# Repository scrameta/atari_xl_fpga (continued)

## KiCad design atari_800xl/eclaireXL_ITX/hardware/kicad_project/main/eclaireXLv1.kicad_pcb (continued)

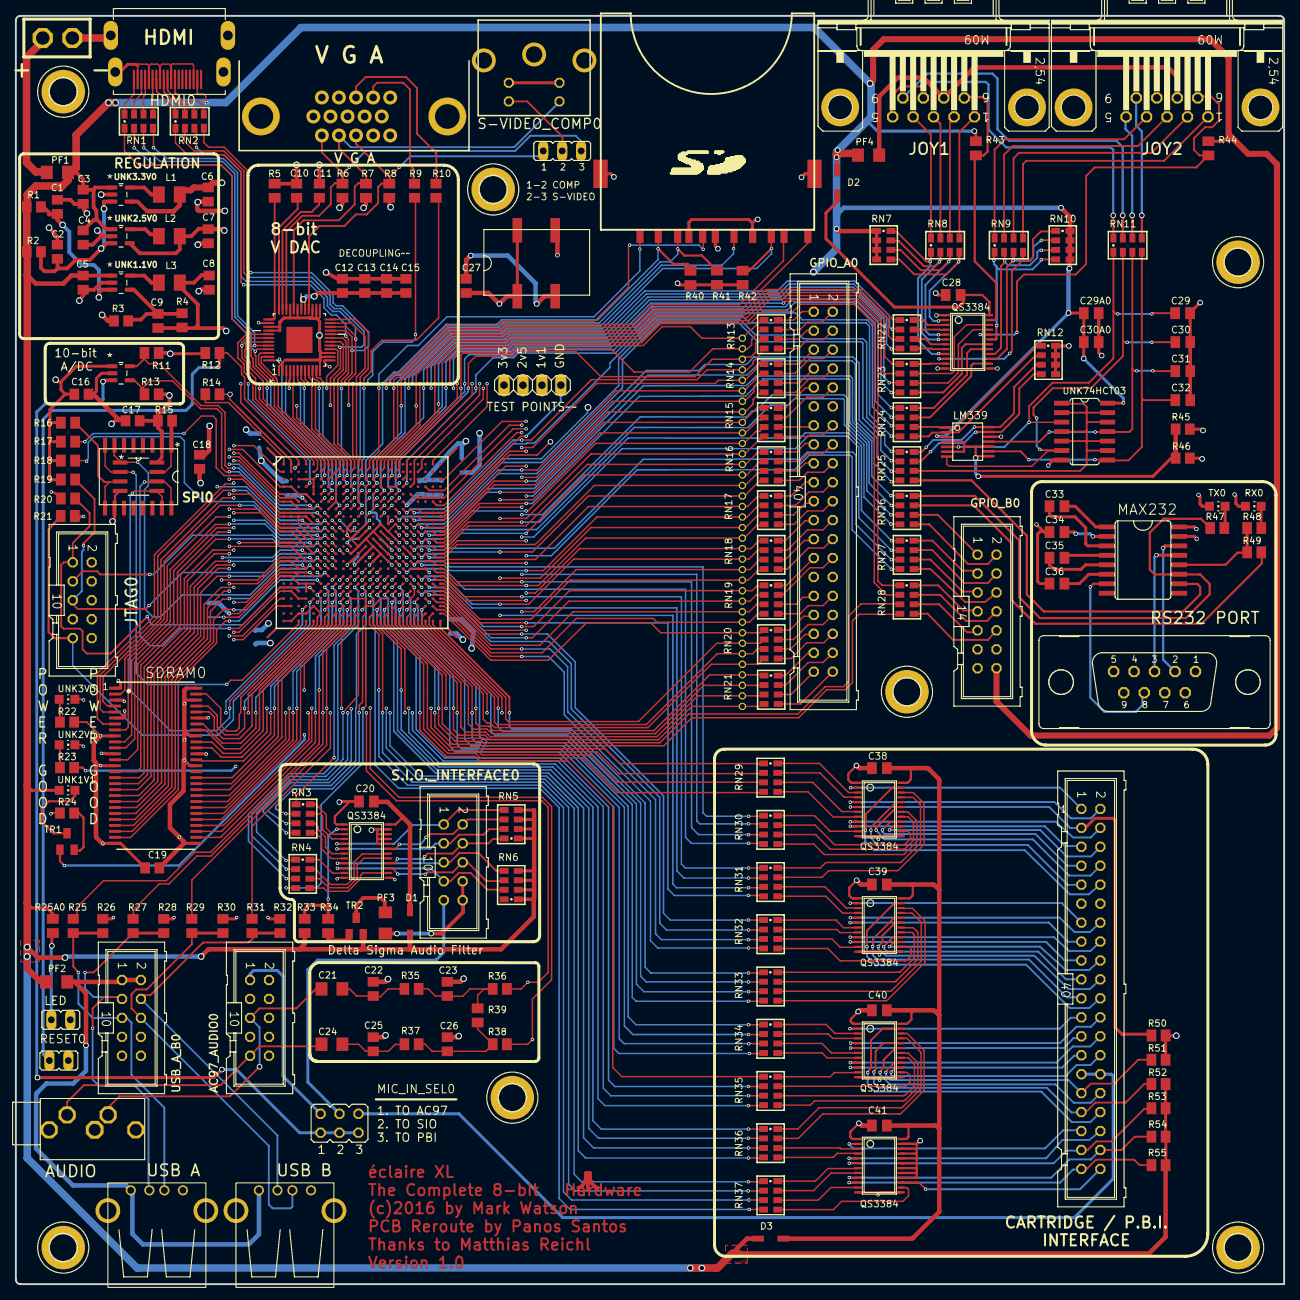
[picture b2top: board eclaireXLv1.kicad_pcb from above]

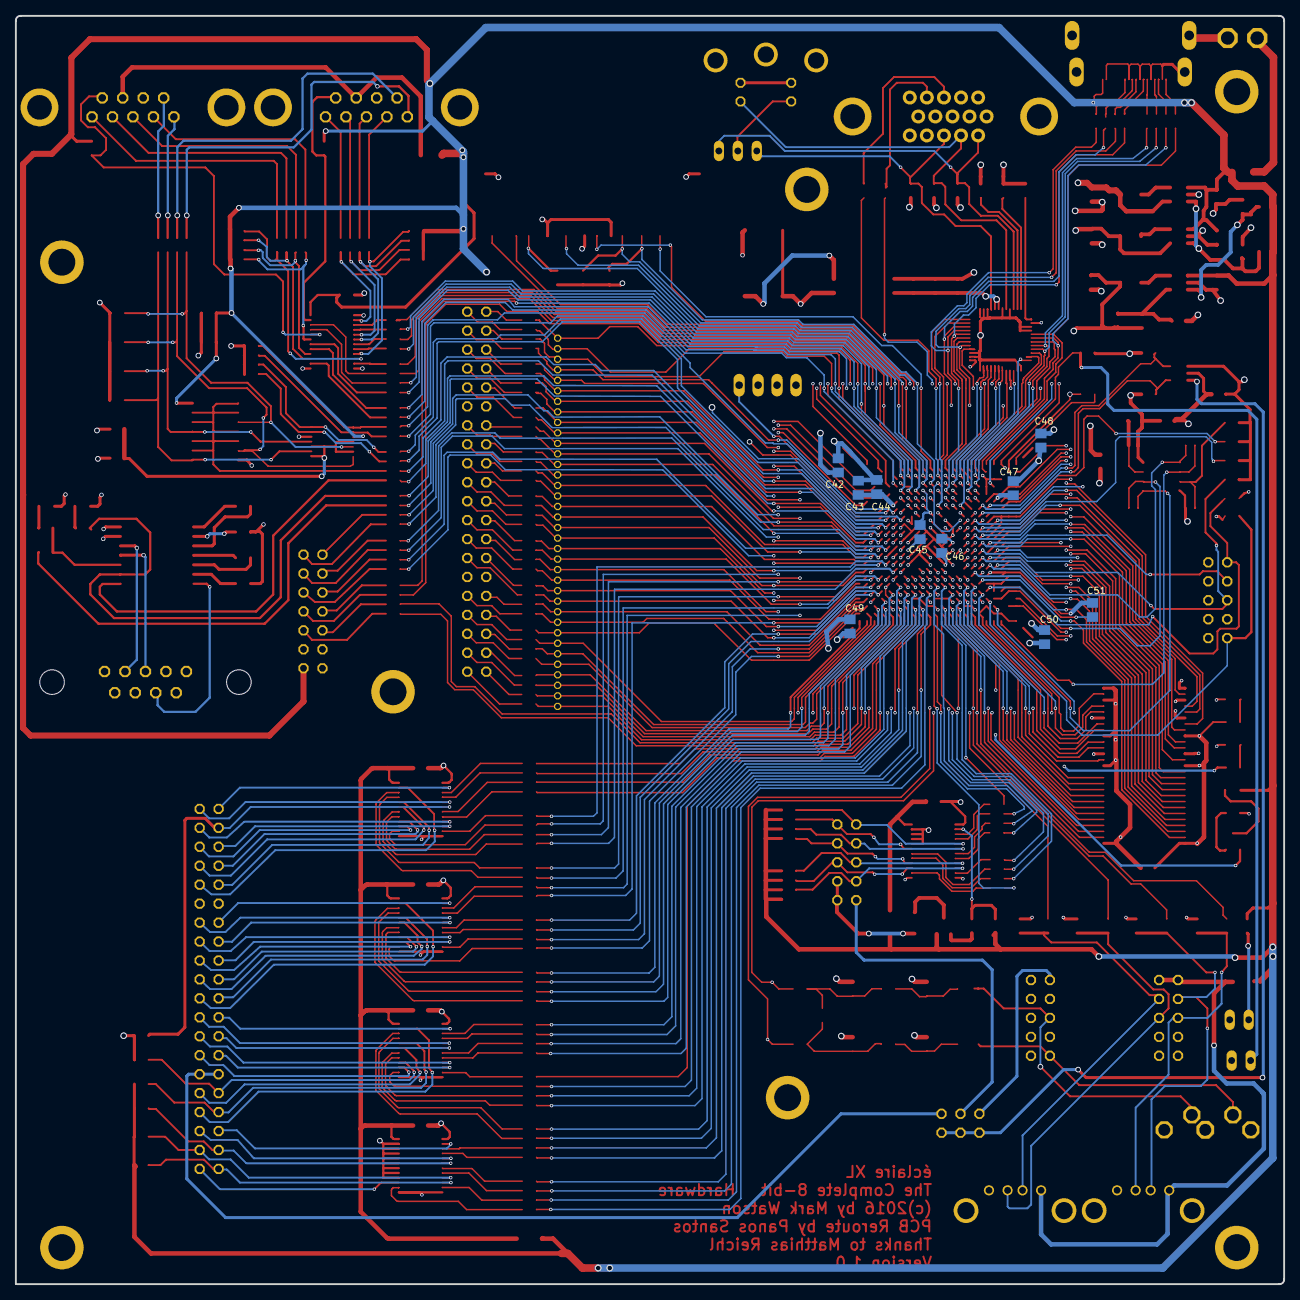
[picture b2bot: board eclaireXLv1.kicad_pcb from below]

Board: 4 copper layers, 170.0 x 170.0 mm, 211 parts (10 on the bottom side), 453 nets.

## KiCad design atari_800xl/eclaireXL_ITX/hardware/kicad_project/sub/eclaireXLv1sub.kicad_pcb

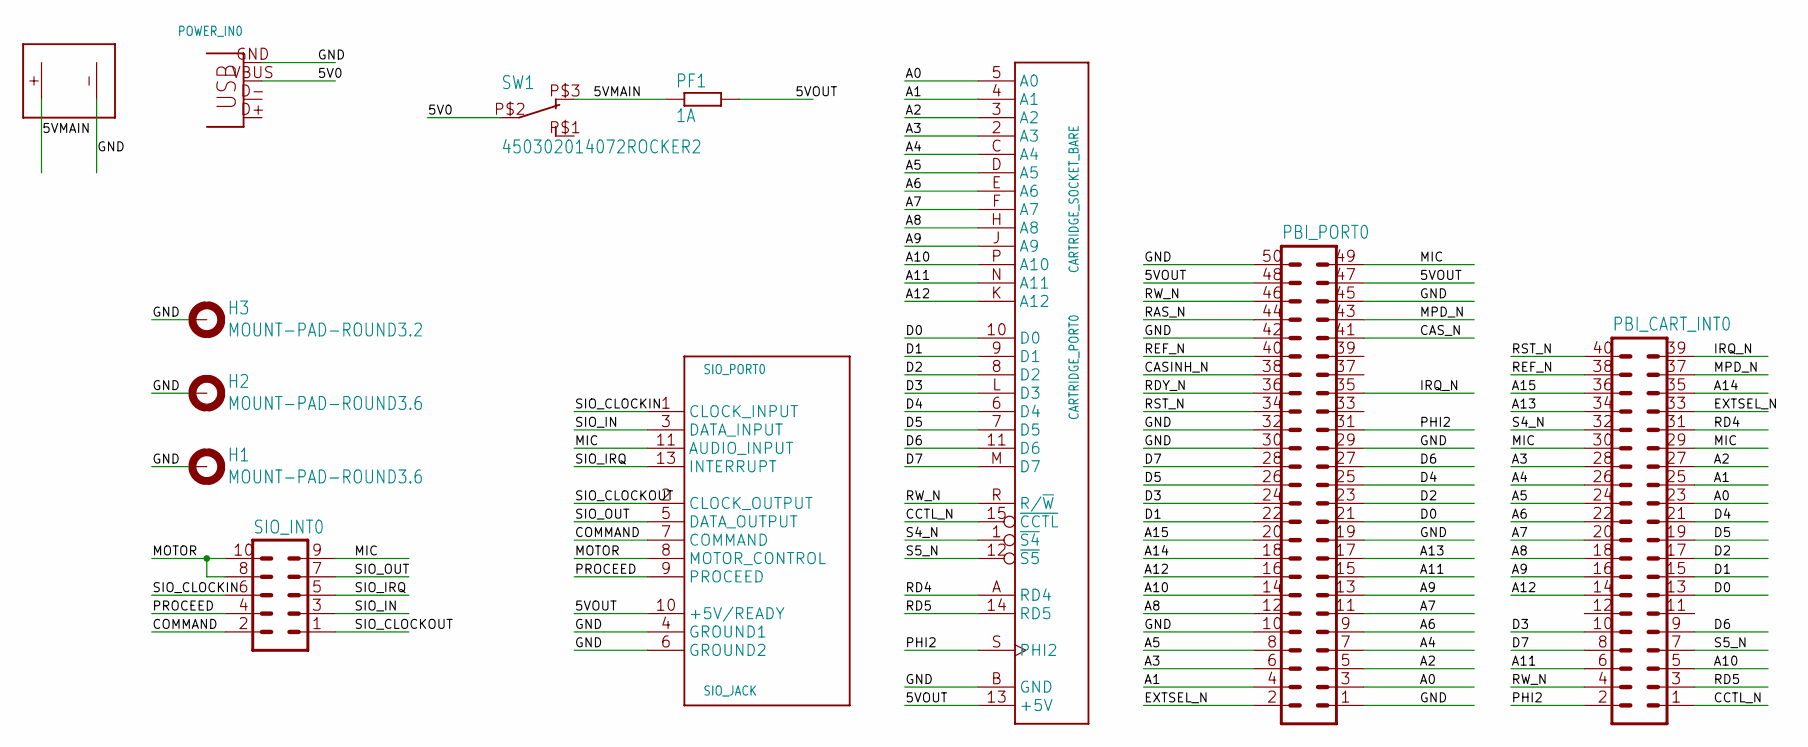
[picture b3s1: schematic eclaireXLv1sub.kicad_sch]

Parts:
CARTRIDGE_PORT0: CARTRIDGE_SOCKET_BARE; CARTRIDGE_SOCKET
H1, H2: MOUNT-PAD-ROUND3.6; 3,6-PAD
H3: MOUNT-PAD-ROUND3.2; 3,2-PAD
PBI_CART_INT0: ML40
PBI_PORT0: ML50
PF1: 1A; R1206
POWER_IN0: USB-B-H
SIO_INT0: ML10
SIO_PORT0: SIO_JACK
SW1: 450302014072ROCKER2; ROCKER_VERT_SPDT2
U$6: MOLEX_PS

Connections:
5V0: POWER_IN0.VBUS, SW1.P$2 (1)
5VMAIN: PF1.1, SW1.P$3 (3), U$6.+
5VOUT: CARTRIDGE_PORT0.13 (+5V), PBI_PORT0.47, PBI_PORT0.48, PF1.2, SIO_PORT0.10 (+5V/READY)
A0: CARTRIDGE_PORT0.5 (A0), PBI_CART_INT0.23, PBI_PORT0.3
A1: CARTRIDGE_PORT0.4 (A1), PBI_CART_INT0.25, PBI_PORT0.4
A2: CARTRIDGE_PORT0.3 (A2), PBI_CART_INT0.27, PBI_PORT0.5
A3: CARTRIDGE_PORT0.2 (A3), PBI_CART_INT0.28, PBI_PORT0.6
A4: CARTRIDGE_PORT0.C (A4), PBI_CART_INT0.26, PBI_PORT0.7
A5: CARTRIDGE_PORT0.D (A5), PBI_CART_INT0.24, PBI_PORT0.8
A6: CARTRIDGE_PORT0.E (A6), PBI_CART_INT0.22, PBI_PORT0.9
A7: CARTRIDGE_PORT0.F (A7), PBI_CART_INT0.20, PBI_PORT0.11
A8: CARTRIDGE_PORT0.H (A8), PBI_CART_INT0.18, PBI_PORT0.12
A9: CARTRIDGE_PORT0.J (A9), PBI_CART_INT0.16, PBI_PORT0.13
A10: CARTRIDGE_PORT0.P (A10), PBI_CART_INT0.5, PBI_PORT0.14
A11: CARTRIDGE_PORT0.N (A11), PBI_CART_INT0.6, PBI_PORT0.15
A12: CARTRIDGE_PORT0.K (A12), PBI_CART_INT0.14, PBI_PORT0.16
A13: PBI_CART_INT0.34, PBI_PORT0.17
A14: PBI_CART_INT0.35, PBI_PORT0.18
A15: PBI_CART_INT0.36, PBI_PORT0.20
CASINH_N: PBI_PORT0.38
CAS_N: PBI_PORT0.41
CCTL_N: CARTRIDGE_PORT0.15 (~CCTL), PBI_CART_INT0.1
COMMAND: SIO_INT0.2, SIO_PORT0.7 (COMMAND)
D0: CARTRIDGE_PORT0.10 (D0), PBI_CART_INT0.13, PBI_PORT0.21
D1: CARTRIDGE_PORT0.9 (D1), PBI_CART_INT0.15, PBI_PORT0.22
D2: CARTRIDGE_PORT0.8 (D2), PBI_CART_INT0.17, PBI_PORT0.23
D3: CARTRIDGE_PORT0.L (D3), PBI_CART_INT0.10, PBI_PORT0.24
D4: CARTRIDGE_PORT0.6 (D4), PBI_CART_INT0.21, PBI_PORT0.25
D5: CARTRIDGE_PORT0.7 (D5), PBI_CART_INT0.19, PBI_PORT0.26
D6: CARTRIDGE_PORT0.11 (D6), PBI_CART_INT0.9, PBI_PORT0.27
D7: CARTRIDGE_PORT0.M (D7), PBI_CART_INT0.8, PBI_PORT0.28
EXTSEL_N: PBI_CART_INT0.33, PBI_PORT0.2
GND: CARTRIDGE_PORT0.B (GND), H1.B3,6, H2.B3,6, H3.B3,2, PBI_PORT0.1, PBI_PORT0.10, PBI_PORT0.19, PBI_PORT0.29, PBI_PORT0.30, PBI_PORT0.32, PBI_PORT0.42, PBI_PORT0.45, PBI_PORT0.50, POWER_IN0.GND, SIO_PORT0.4 (GROUND1), SIO_PORT0.6 (GROUND2), U$6.- (--)
IRQ_N: PBI_CART_INT0.39, PBI_PORT0.35
MIC: PBI_CART_INT0.29, PBI_CART_INT0.30, PBI_PORT0.49, SIO_INT0.9, SIO_PORT0.11 (AUDIO_INPUT)
MOTOR: SIO_INT0.8, SIO_INT0.10, SIO_PORT0.8 (MOTOR_CONTROL)
MPD_N: PBI_CART_INT0.37, PBI_PORT0.43
PHI2: CARTRIDGE_PORT0.S (PHI2), PBI_CART_INT0.2, PBI_PORT0.31
PROCEED: SIO_INT0.4, SIO_PORT0.9 (PROCEED)
RAS_N: PBI_PORT0.44
RD4: CARTRIDGE_PORT0.A (RD4), PBI_CART_INT0.31
RD5: CARTRIDGE_PORT0.14 (RD5), PBI_CART_INT0.3
RDY_N: PBI_PORT0.36
REF_N: PBI_CART_INT0.38, PBI_PORT0.40
RST_N: PBI_CART_INT0.40, PBI_PORT0.34
RW_N: CARTRIDGE_PORT0.R (R/~W), PBI_CART_INT0.4, PBI_PORT0.46
S4_N: CARTRIDGE_PORT0.1 (~S4), PBI_CART_INT0.32
S5_N: CARTRIDGE_PORT0.12 (~S5), PBI_CART_INT0.7
SIO_CLOCKIN: SIO_INT0.6, SIO_PORT0.1 (CLOCK_INPUT)
SIO_CLOCKOUT: SIO_INT0.1, SIO_PORT0.2 (CLOCK_OUTPUT)
SIO_IN: SIO_INT0.3, SIO_PORT0.3 (DATA_INPUT)
SIO_IRQ: SIO_INT0.5, SIO_PORT0.13 (INTERRUPT)
SIO_OUT: SIO_INT0.7, SIO_PORT0.5 (DATA_OUTPUT)

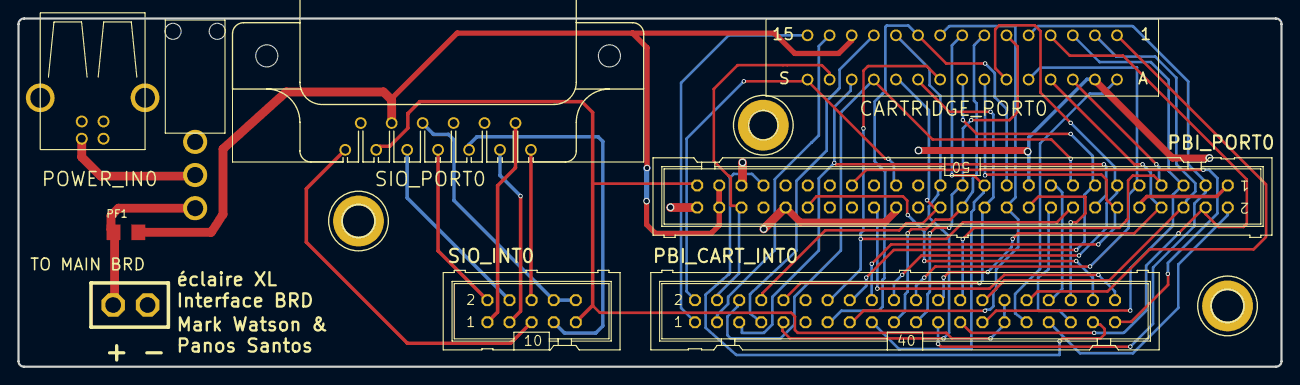
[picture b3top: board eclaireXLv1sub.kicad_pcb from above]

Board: 4 copper layers, 145.1 x 40.0 mm, 12 parts (0 on the bottom side), 49 nets.

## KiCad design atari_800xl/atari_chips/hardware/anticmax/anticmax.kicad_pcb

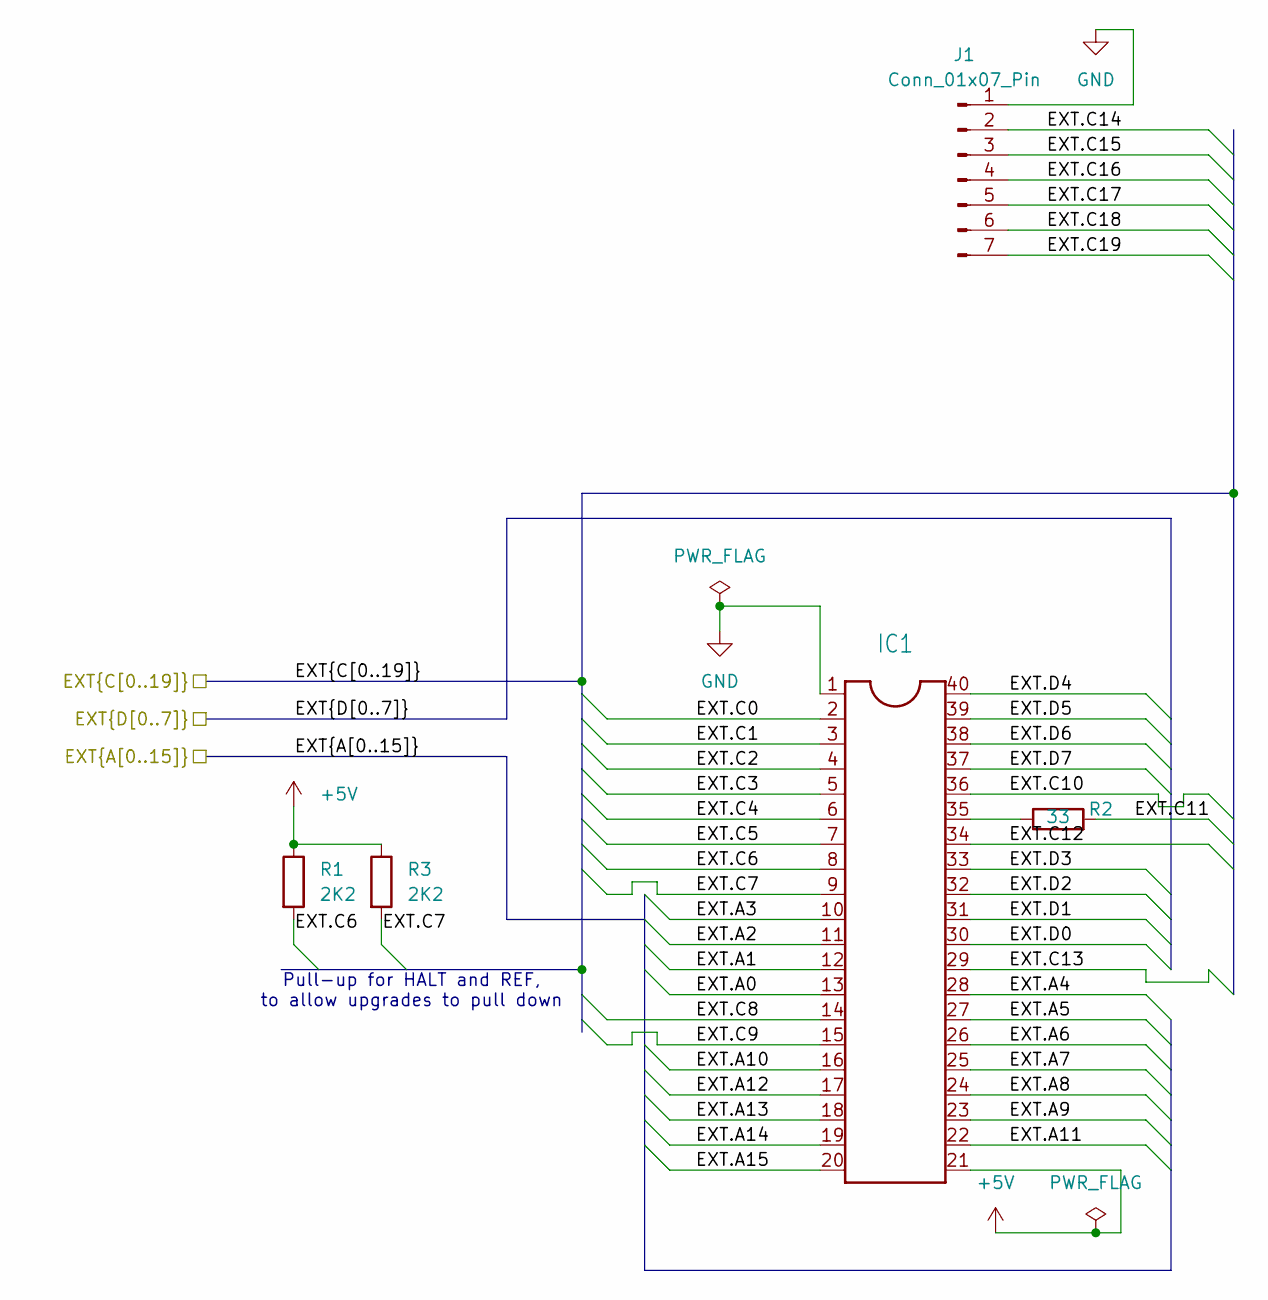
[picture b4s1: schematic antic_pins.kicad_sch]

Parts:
IC1: DIL40
J1: Conn_01x07_Pin; PinHeader_1x07_P2.54mm_Vertical
R1, R3: 2K2; R_0603_1608Metric
R2: 33; R_0603_1608Metric

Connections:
+5V: IC1.21, R1.1, R3.1; also elsewhere on the board
/Bus drivers/EXT.A0: IC1.13; also elsewhere on the board
/Bus drivers/EXT.A1: IC1.12; also elsewhere on the board
/Bus drivers/EXT.A2: IC1.11; also elsewhere on the board
/Bus drivers/EXT.A3: IC1.10; also elsewhere on the board
/Bus drivers/EXT.A4: IC1.28; also elsewhere on the board
/Bus drivers/EXT.A5: IC1.27; also elsewhere on the board
/Bus drivers/EXT.A6: IC1.26; also elsewhere on the board
/Bus drivers/EXT.A7: IC1.25; also elsewhere on the board
/Bus drivers/EXT.A8: IC1.24; also elsewhere on the board
/Bus drivers/EXT.A9: IC1.23; also elsewhere on the board
/Bus drivers/EXT.A10: IC1.16; also elsewhere on the board
/Bus drivers/EXT.A11: IC1.22; also elsewhere on the board
/Bus drivers/EXT.A12: IC1.17; also elsewhere on the board
/Bus drivers/EXT.A13: IC1.18; also elsewhere on the board
/Bus drivers/EXT.A14: IC1.19; also elsewhere on the board
/Bus drivers/EXT.A15: IC1.20; also elsewhere on the board
/Bus drivers/EXT.D0: IC1.30; also elsewhere on the board
/Bus drivers/EXT.D1: IC1.31; also elsewhere on the board
/Bus drivers/EXT.D2: IC1.32; also elsewhere on the board
/Bus drivers/EXT.D3: IC1.33; also elsewhere on the board
/Bus drivers/EXT.D4: IC1.40; also elsewhere on the board
/Bus drivers/EXT.D5: IC1.39; also elsewhere on the board
/Bus drivers/EXT.D6: IC1.38; also elsewhere on the board
/Bus drivers/EXT.D7: IC1.37; also elsewhere on the board
/antic_pins/EXT.C0: IC1.2; also elsewhere on the board
/antic_pins/EXT.C1: IC1.3; also elsewhere on the board
/antic_pins/EXT.C2: IC1.4; also elsewhere on the board
/antic_pins/EXT.C3: IC1.5; also elsewhere on the board
/antic_pins/EXT.C4: IC1.6; also elsewhere on the board
/antic_pins/EXT.C5: IC1.7; also elsewhere on the board
/antic_pins/EXT.C6: IC1.8, R1.2; also elsewhere on the board
/antic_pins/EXT.C7: IC1.9, R3.2; also elsewhere on the board
/antic_pins/EXT.C8: IC1.14; also elsewhere on the board
/antic_pins/EXT.C9: IC1.15; also elsewhere on the board
/antic_pins/EXT.C10: IC1.36; also elsewhere on the board
/antic_pins/EXT.C11: R2.2; also elsewhere on the board
/antic_pins/EXT.C12: IC1.34; also elsewhere on the board
/antic_pins/EXT.C13: IC1.29; also elsewhere on the board
/antic_pins/EXT.C14: J1.2; also elsewhere on the board
/antic_pins/EXT.C15: J1.3; also elsewhere on the board
/antic_pins/EXT.C16: J1.4; also elsewhere on the board
/antic_pins/EXT.C17: J1.5; also elsewhere on the board
/antic_pins/EXT.C18: J1.6; also elsewhere on the board
/antic_pins/EXT.C19: J1.7; also elsewhere on the board
GND: IC1.1, J1.1; also elsewhere on the board
unnamed: IC1.35, R2.1

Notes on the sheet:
Pull-up for HALT and REF, to allow upgrades to pull down

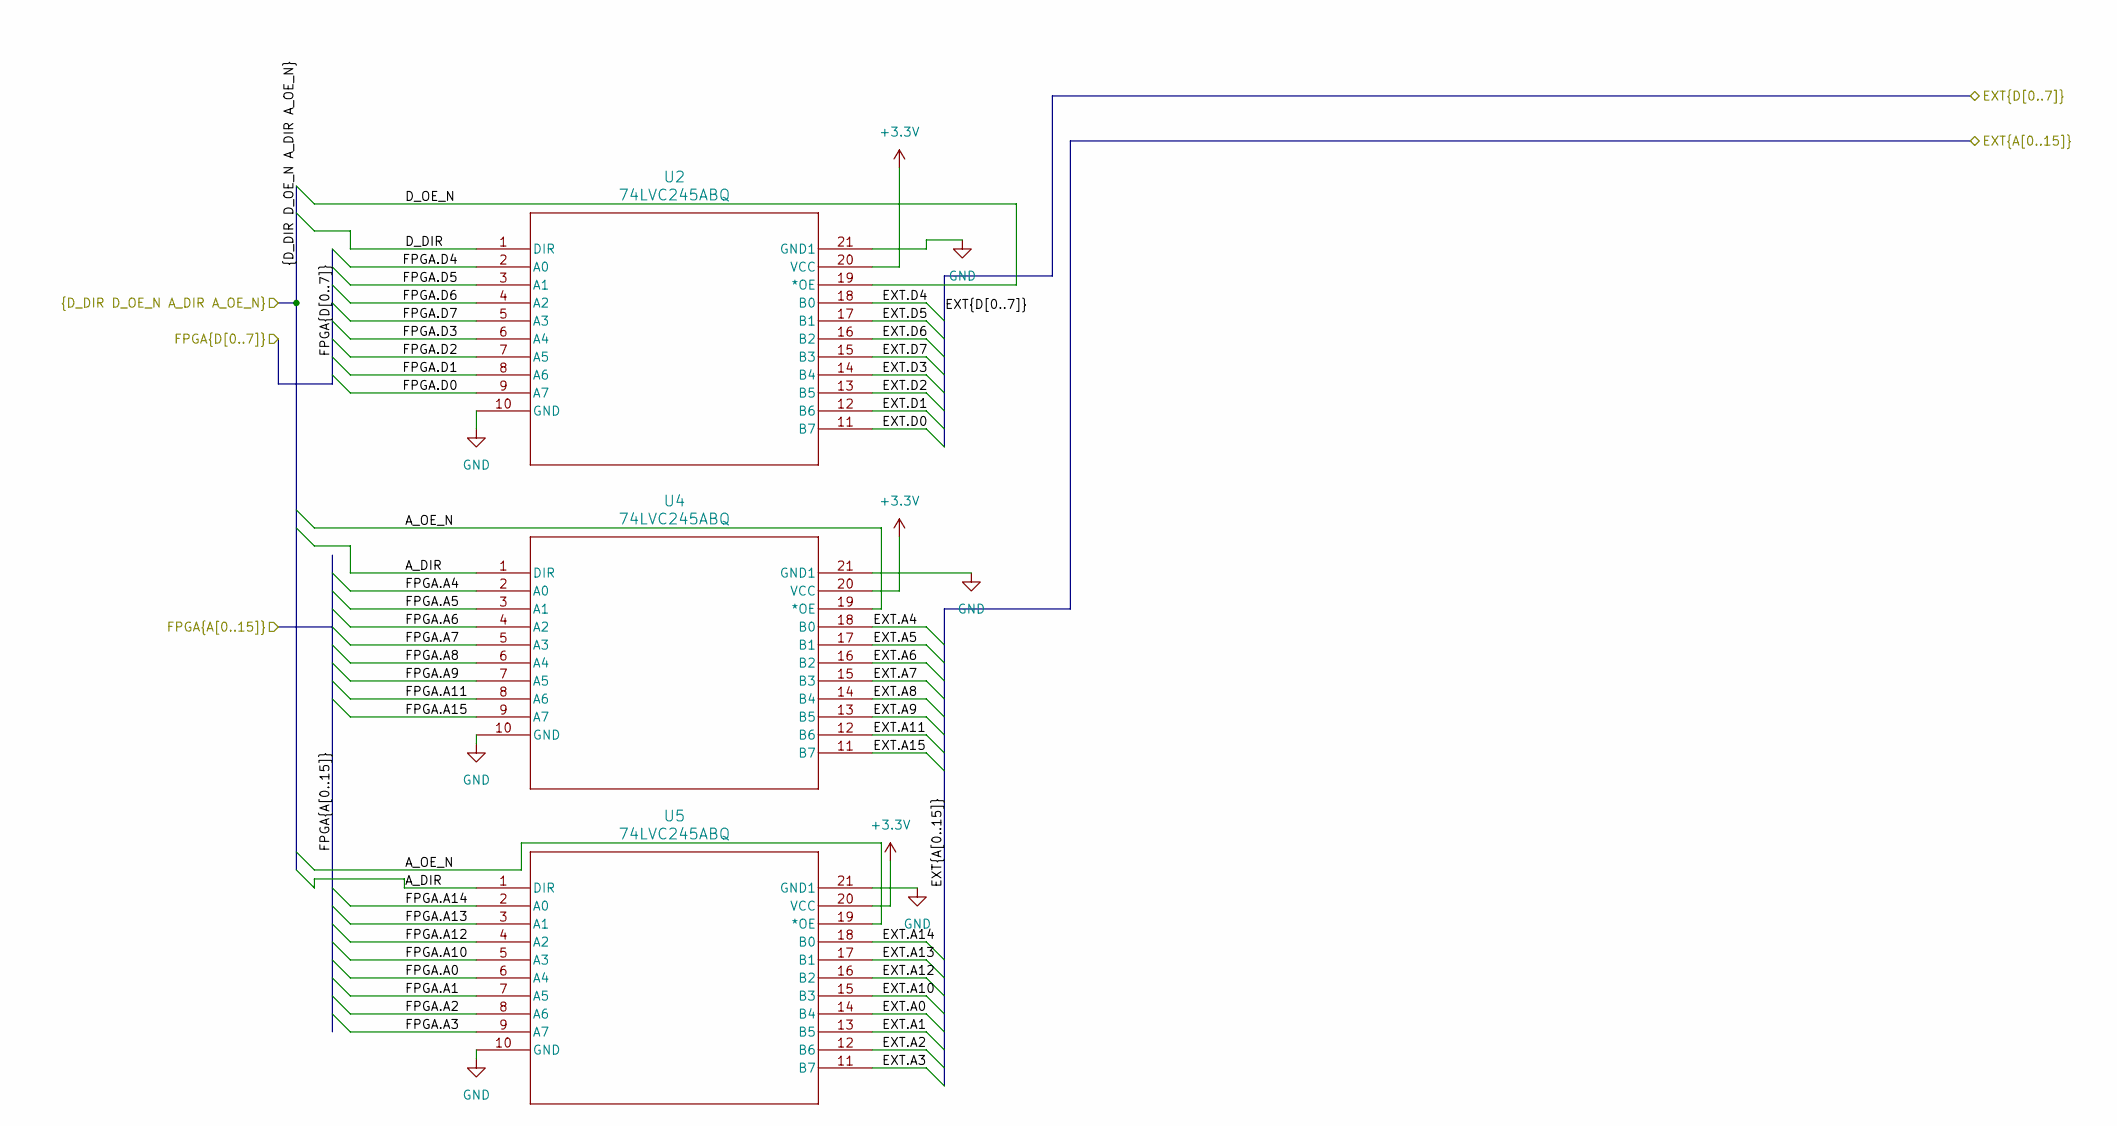
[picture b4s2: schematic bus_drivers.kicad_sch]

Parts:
U2, U4, U5: 74LVC245ABQ; SOT764-1_NXP

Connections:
+3.3V: U2.20 (VCC), U4.20 (VCC), U5.20 (VCC); also elsewhere on the board
/Bus drivers/A_DIR: U4.1 (DIR), U5.1 (DIR); also elsewhere on the board
/Bus drivers/A_OE_N: U4.19 (*OE), U5.19 (*OE); also elsewhere on the board
/Bus drivers/D_DIR: U2.1 (DIR); also elsewhere on the board
/Bus drivers/D_OE_N: U2.19 (*OE); also elsewhere on the board
/Bus drivers/EXT.A0: U5.14 (B4); also elsewhere on the board
/Bus drivers/EXT.A1: U5.13 (B5); also elsewhere on the board
/Bus drivers/EXT.A2: U5.12 (B6); also elsewhere on the board
/Bus drivers/EXT.A3: U5.11 (B7); also elsewhere on the board
/Bus drivers/EXT.A4: U4.18 (B0); also elsewhere on the board
/Bus drivers/EXT.A5: U4.17 (B1); also elsewhere on the board
/Bus drivers/EXT.A6: U4.16 (B2); also elsewhere on the board
/Bus drivers/EXT.A7: U4.15 (B3); also elsewhere on the board
/Bus drivers/EXT.A8: U4.14 (B4); also elsewhere on the board
/Bus drivers/EXT.A9: U4.13 (B5); also elsewhere on the board
/Bus drivers/EXT.A10: U5.15 (B3); also elsewhere on the board
/Bus drivers/EXT.A11: U4.12 (B6); also elsewhere on the board
/Bus drivers/EXT.A12: U5.16 (B2); also elsewhere on the board
/Bus drivers/EXT.A13: U5.17 (B1); also elsewhere on the board
/Bus drivers/EXT.A14: U5.18 (B0); also elsewhere on the board
/Bus drivers/EXT.A15: U4.11 (B7); also elsewhere on the board
/Bus drivers/EXT.D0: U2.11 (B7); also elsewhere on the board
/Bus drivers/EXT.D1: U2.12 (B6); also elsewhere on the board
/Bus drivers/EXT.D2: U2.13 (B5); also elsewhere on the board
/Bus drivers/EXT.D3: U2.14 (B4); also elsewhere on the board
/Bus drivers/EXT.D4: U2.18 (B0); also elsewhere on the board
/Bus drivers/EXT.D5: U2.17 (B1); also elsewhere on the board
/Bus drivers/EXT.D6: U2.16 (B2); also elsewhere on the board
/Bus drivers/EXT.D7: U2.15 (B3); also elsewhere on the board
/Bus drivers/FPGA.A0: U5.6 (A4); also elsewhere on the board
/Bus drivers/FPGA.A1: U5.7 (A5); also elsewhere on the board
/Bus drivers/FPGA.A2: U5.8 (A6); also elsewhere on the board
/Bus drivers/FPGA.A3: U5.9 (A7); also elsewhere on the board
/Bus drivers/FPGA.A4: U4.2 (A0); also elsewhere on the board
/Bus drivers/FPGA.A5: U4.3 (A1); also elsewhere on the board
/Bus drivers/FPGA.A6: U4.4 (A2); also elsewhere on the board
/Bus drivers/FPGA.A7: U4.5 (A3); also elsewhere on the board
/Bus drivers/FPGA.A8: U4.6 (A4); also elsewhere on the board
/Bus drivers/FPGA.A9: U4.7 (A5); also elsewhere on the board
/Bus drivers/FPGA.A10: U5.5 (A3); also elsewhere on the board
/Bus drivers/FPGA.A11: U4.8 (A6); also elsewhere on the board
/Bus drivers/FPGA.A12: U5.4 (A2); also elsewhere on the board
/Bus drivers/FPGA.A13: U5.3 (A1); also elsewhere on the board
/Bus drivers/FPGA.A14: U5.2 (A0); also elsewhere on the board
/Bus drivers/FPGA.A15: U4.9 (A7); also elsewhere on the board
/Bus drivers/FPGA.D0: U2.9 (A7); also elsewhere on the board
/Bus drivers/FPGA.D1: U2.8 (A6); also elsewhere on the board
/Bus drivers/FPGA.D2: U2.7 (A5); also elsewhere on the board
/Bus drivers/FPGA.D3: U2.6 (A4); also elsewhere on the board
/Bus drivers/FPGA.D4: U2.2 (A0); also elsewhere on the board
/Bus drivers/FPGA.D5: U2.3 (A1); also elsewhere on the board
/Bus drivers/FPGA.D6: U2.4 (A2); also elsewhere on the board
/Bus drivers/FPGA.D7: U2.5 (A3); also elsewhere on the board
GND: U2.10 (GND), U2.21 (GND1), U4.10 (GND), U4.21 (GND1), U5.10 (GND), U5.21 (GND1); also elsewhere on the board

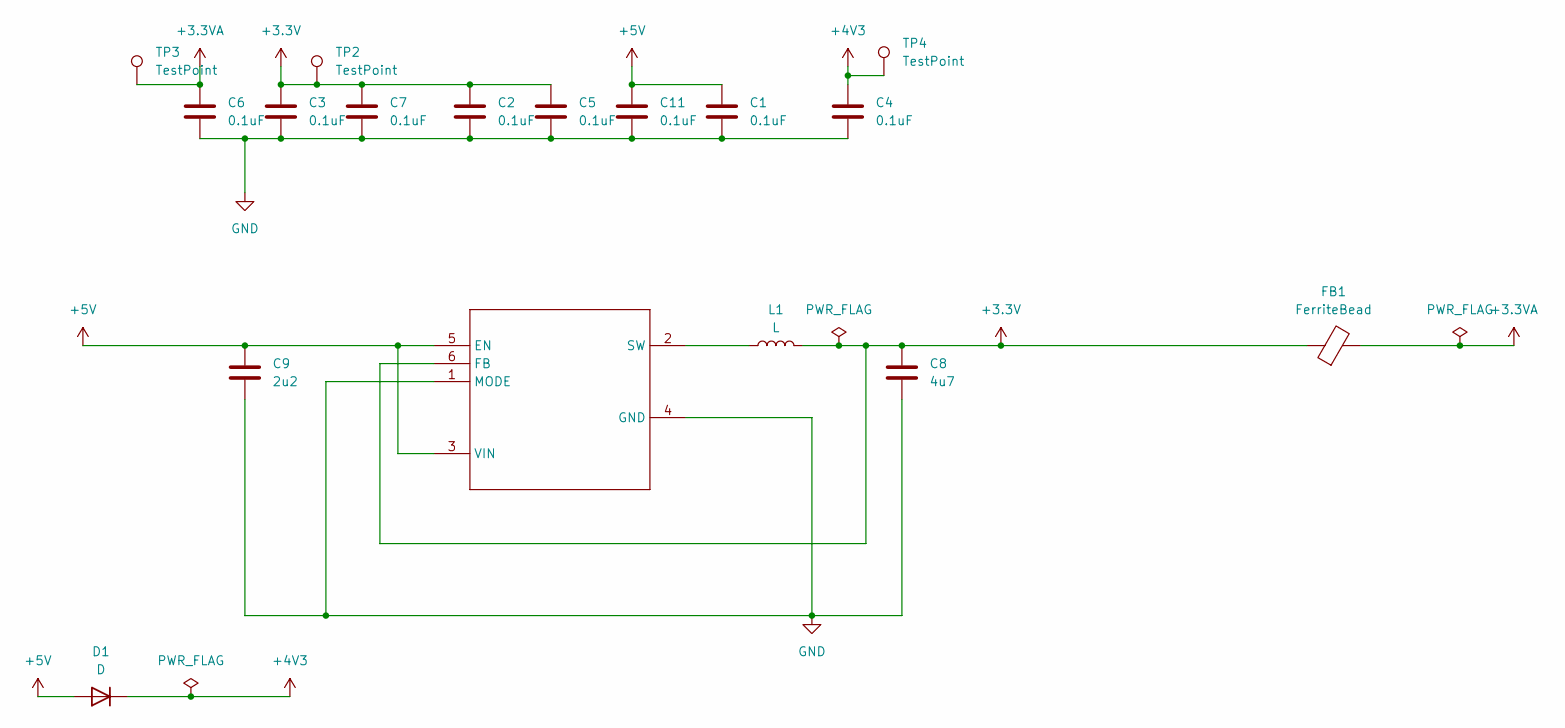
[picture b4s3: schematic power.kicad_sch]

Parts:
C1, C2, C3, C4, C5, C6, C7, C11: 0.1uF; C_0603_1608Metric
C8: 4u7; C_0603_1608Metric
C9: 2u2; C_0603_1608Metric
D1: D; D_0603_1608Metric
FB1: FerriteBead; L_0603_1608Metric
L1: L; L_1008_2520Metric_Pad1.43x2.20mm_HandSolder
TP2, TP3, TP4: TestPoint; TestPoint_THTPad_D1.5mm_Drill0.7mm
U7: DRY6

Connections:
+3.3V: C2.1, C3.1, C5.1, C7.1, C8.1, FB1.1, L1.2, TP2.1, U7.6 (FB); also elsewhere on the board
+3.3VA: C6.1, FB1.2, TP3.1; also elsewhere on the board
+4V3: C4.1, D1.1 (K), TP4.1; also elsewhere on the board
+5V: C1.1, C9.1, C11.1, D1.2 (A), U7.3 (VIN), U7.5 (EN); also elsewhere on the board
GND: C1.2, C2.2, C3.2, C4.2, C5.2, C6.2, C7.2, C8.2, C9.2, C11.2, U7.1 (MODE), U7.4 (GND); also elsewhere on the board
unnamed: L1.1, U7.2 (SW)

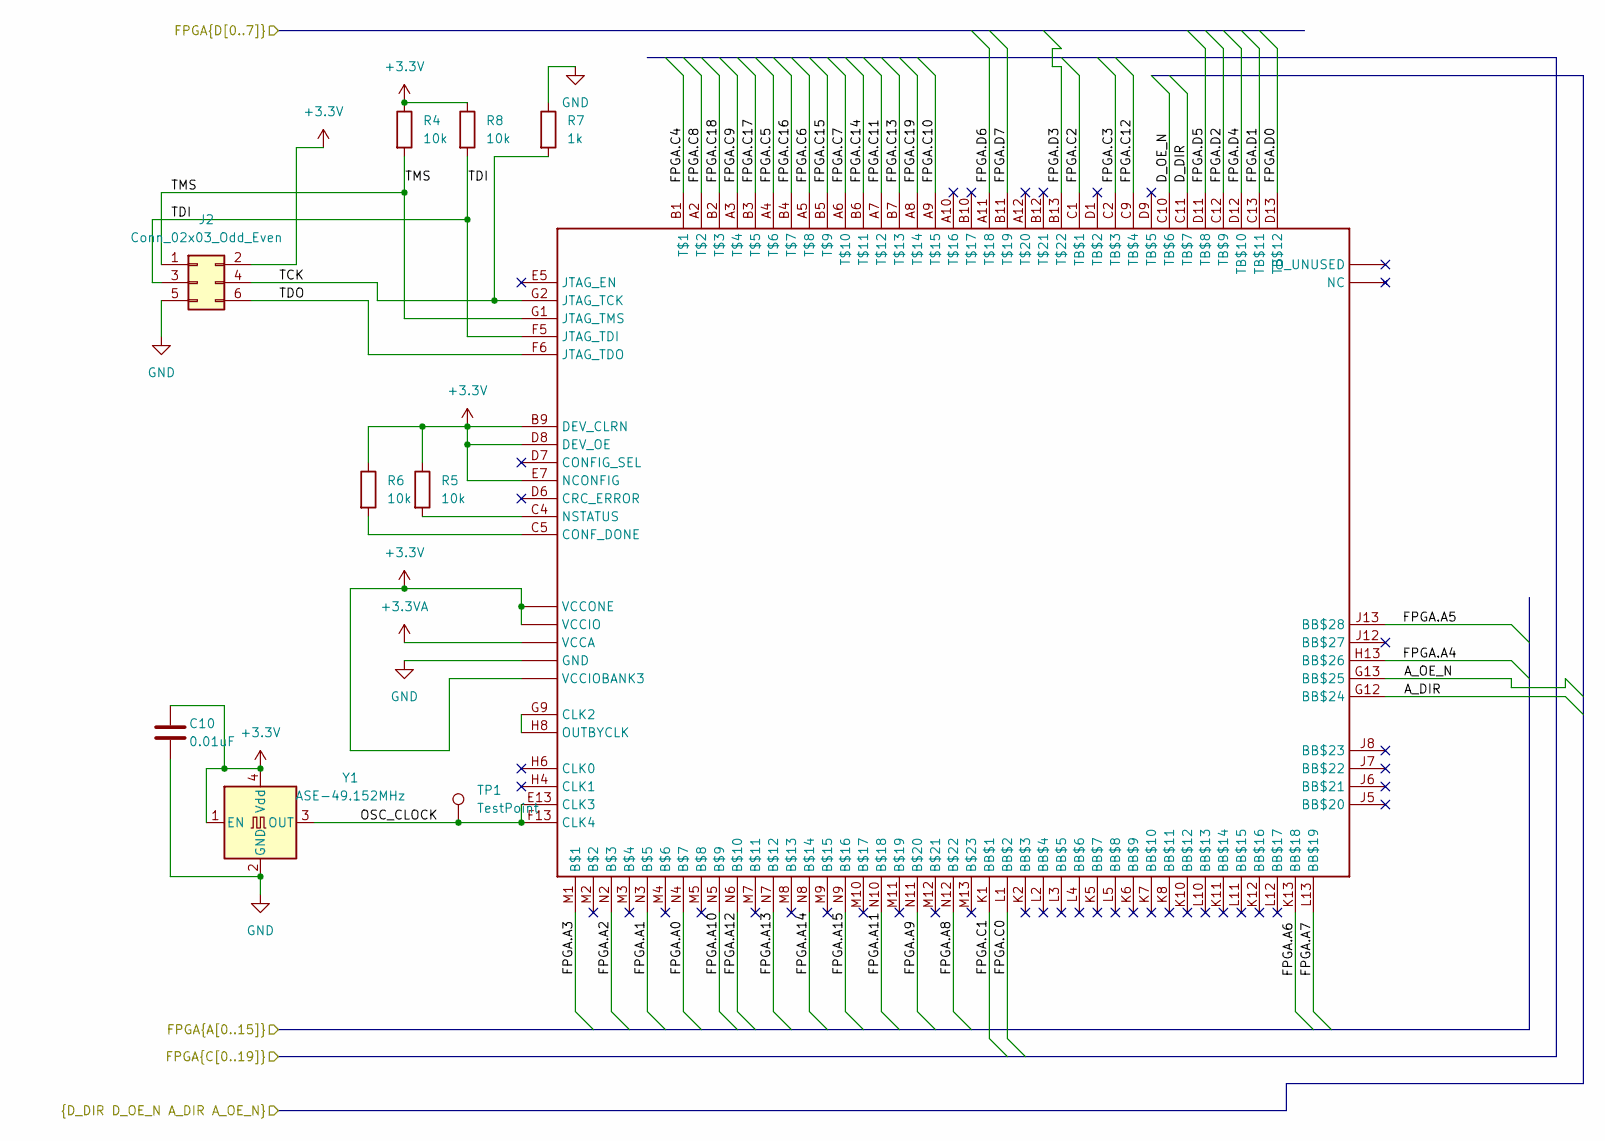
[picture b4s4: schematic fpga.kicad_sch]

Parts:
C10: 0.01uF; C_0603_1608Metric
J2: Conn_02x03_Odd_Even; PinHeader_2x03_P2.54mm_Vertical
R4, R5, R6, R8: 10k; R_0603_1608Metric
R7: 1k; R_0603_1608Metric
TP1: TestPoint; TestPoint_THTPad_D1.5mm_Drill0.7mm
U6: 10M16SAU169I7G; U169SMALL
Y1: ASE-49.152MHz; Oscillator_SMD_Abracon_ASE-4Pin_3.2x2.5mm

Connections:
+3.3V: C10.1, J2.2, R4.1, R5.1, R6.1, R8.1, U6.B9 (DEV_CLRN), U6.C6 (VCCIO), U6.C7 (VCCIO), U6.C8 (VCCIO), U6.D8 (DEV_OE), U6.E7 (NCONFIG), U6.F2 (VCCIO), U6.F7 (VCCONE), U6.F11 (VCCIO), U6.G3 (VCCIO), U6.G6 (VCCONE), U6.G8 (VCCONE), U6.G11 (VCCIO), U6.H7 (VCCONE), U6.H11 (VCCIO), U6.J3 (VCCIO), U6.J11 (VCCIO), U6.K3 (VCCIO), U6.L6 (VCCIOBANK3), U6.L7 (VCCIOBANK3), U6.L8 (VCCIOBANK3), Y1.1 (EN), Y1.4 (Vdd); also elsewhere on the board
+3.3VA: U6.D4 (VCCA), U6.D10 (VCCA), U6.K4 (VCCA), U6.K9 (VCCA); also elsewhere on the board
/Bus drivers/A_DIR: U6.G12 (BB$24); also elsewhere on the board
/Bus drivers/A_OE_N: U6.G13 (BB$25); also elsewhere on the board
/Bus drivers/D_DIR: U6.C11 (TB$7); also elsewhere on the board
/Bus drivers/D_OE_N: U6.C10 (TB$6); also elsewhere on the board
/Bus drivers/FPGA.A0: U6.N4; also elsewhere on the board
/Bus drivers/FPGA.A1: U6.N3; also elsewhere on the board
/Bus drivers/FPGA.A2: U6.N2; also elsewhere on the board
/Bus drivers/FPGA.A3: U6.M1; also elsewhere on the board
/Bus drivers/FPGA.A4: U6.H13 (BB$26); also elsewhere on the board
/Bus drivers/FPGA.A5: U6.J13 (BB$28); also elsewhere on the board
/Bus drivers/FPGA.A6: U6.K13 (BB$18); also elsewhere on the board
/Bus drivers/FPGA.A7: U6.L13 (BB$19); also elsewhere on the board
/Bus drivers/FPGA.A8: U6.N12; also elsewhere on the board
/Bus drivers/FPGA.A9: U6.N11; also elsewhere on the board
/Bus drivers/FPGA.A10: U6.N5; also elsewhere on the board
/Bus drivers/FPGA.A11: U6.N10; also elsewhere on the board
/Bus drivers/FPGA.A12: U6.N6; also elsewhere on the board
/Bus drivers/FPGA.A13: U6.N7; also elsewhere on the board
/Bus drivers/FPGA.A14: U6.N8; also elsewhere on the board
/Bus drivers/FPGA.A15: U6.N9; also elsewhere on the board
/Bus drivers/FPGA.D0: U6.D13 (TB$12); also elsewhere on the board
/Bus drivers/FPGA.D1: U6.C13 (TB$11); also elsewhere on the board
/Bus drivers/FPGA.D2: U6.C12 (TB$9); also elsewhere on the board
/Bus drivers/FPGA.D3: U6.B13; also elsewhere on the board
/Bus drivers/FPGA.D4: U6.D12 (TB$10); also elsewhere on the board
/Bus drivers/FPGA.D5: U6.D11 (TB$8); also elsewhere on the board
/Bus drivers/FPGA.D6: U6.A11; also elsewhere on the board
/Bus drivers/FPGA.D7: U6.B11; also elsewhere on the board
/FPGA/OSC_CLOCK: TP1.1, U6.E13 (CLK3), U6.F13 (CLK4), Y1.3 (OUT)
/FPGA/TCK: J2.4, R7.2, U6.G2 (JTAG_TCK)
/FPGA/TDI: J2.3, R8.2, U6.F5 (JTAG_TDI)
/FPGA/TDO: J2.6, U6.F6 (JTAG_TDO)
/FPGA/TMS: J2.1, R4.2, U6.G1 (JTAG_TMS)
/level shifters/FPGA.C0: U6.L1 (BB$2); also elsewhere on the board
/level shifters/FPGA.C1: U6.K1 (BB$1); also elsewhere on the board
/level shifters/FPGA.C2: U6.C1 (TB$1); also elsewhere on the board
/level shifters/FPGA.C3: U6.C2 (TB$3); also elsewhere on the board
/level shifters/FPGA.C4: U6.B1; also elsewhere on the board
/level shifters/FPGA.C5: U6.A4; also elsewhere on the board
/level shifters/FPGA.C6: U6.A5; also elsewhere on the board
/level shifters/FPGA.C7: U6.A6; also elsewhere on the board
/level shifters/FPGA.C8: U6.A2; also elsewhere on the board
/level shifters/FPGA.C9: U6.A3; also elsewhere on the board
/level shifters/FPGA.C10: U6.A9; also elsewhere on the board
/level shifters/FPGA.C11: U6.A7; also elsewhere on the board
/level shifters/FPGA.C12: U6.C9 (TB$4); also elsewhere on the board
/level shifters/FPGA.C13: U6.B7; also elsewhere on the board
/level shifters/FPGA.C14: U6.B6; also elsewhere on the board
/level shifters/FPGA.C15: U6.B5; also elsewhere on the board
/level shifters/FPGA.C16: U6.B4; also elsewhere on the board
/level shifters/FPGA.C17: U6.B3; also elsewhere on the board
/level shifters/FPGA.C18: U6.B2; also elsewhere on the board
/level shifters/FPGA.C19: U6.A8; also elsewhere on the board
GND: C10.2, J2.5, R7.1, U6.A1 (GND), U6.A13 (GND), U6.B8 (GND), U6.C3 (GND), U6.D5 (GND), U6.E11 (GND), U6.F3 (GND), U6.G7 (GND), U6.H12 (GND), U6.J4 (GND), U6.L9 (GND), U6.M6 (GND), U6.N1 (GND), U6.N13 (GND), Y1.2 (GND); also elsewhere on the board
unnamed: U6.G9 (CLK2), U6.H8 (OUTBYCLK)
unnamed: R6.2, U6.C5 (CONF_DONE)
unnamed: R5.2, U6.C4 (NSTATUS)
